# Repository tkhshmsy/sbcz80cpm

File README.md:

# sbcz80cpm
Single Board Computer with Z80 for CP/M

# Features
* Z80 cpu board for CP/M, without any ROM chips
  * supports 128KB to 512KB of SRAM, banked in 32KB
* ATMEGA4809 as I/O Engine sub system
  * Boot loader control
  * UART for console Input/Output
  * Floppy Disk Emulation with SD Card via SPI
  * RTC via I2C
  * other I2C devices

# PCB
## Schematics and Layout

## BOM
| Ref | Name | Qty | Description | Package | Link |
| --- | ---- | --- | ----------- | ------- | ---- |
| U1 | Z80 | 1 | Z80 CPU | DIP40 | Zilog Z84C00*, NEC uPD780C |
| U2 | 74HC32 | 1 | Quad OR | DIP14 | [akizuki](https://akizukidenshi.com/catalog/g/g112877/)|
| U3 | ATMEGA4809 | 1 | ATMEGA4809 | PDIP40 | [akizuki](https://akizukidenshi.com/catalog/g/g116144/)|
| U4 | AS6C4008 | 1 | SRAM | DIP32 | [mouser](https://www.mouser.jp/ProductDetail/Alliance-Memory/AS6C4008-55PCN?qs=E5c5%252Bmu3i3%252BMOyro1Tlhzg%3D%3D)|
| X1 | 1-10MHz | 1 | Crystal OSC | DIP8 | [akizuki 8MHz](https://akizukidenshi.com/catalog/g/g117022/), [akizuki 10MHz](https://akizukidenshi.com/catalog/g/g117023/)|
| C1, C2, C3, C4, C5, C6, C7, C8, C9 | 0.1uF | 9 | | ||
| C10  | 470uF    | 1 | | ||
| R1 | 1K-10K | 1 | for /WAIT control, 10K(-5MHz), 1K(8MHz-)| ||
| R2 | 10K | 1 | for pullup | ||
| R3, R4 | 10K | 2 | for I2C pullup | ||
| R5 | 1K | 1 | for LED | ||
| RN1 | 10Kx4 | 1 | for pullup | |[akizuki](https://akizukidenshi.com/catalog/g/g111909/)|
| RN2 | 10Kx4 | 1 | for IPL control | ||
| RN3 | 10Kx8 | 1 | for IPL control | |[akizuki](https://akizukidenshi.com/catalog/g/g111910/)|
| D1 | LED | 1 | 3mm | ||
| SW1 | Push Button | 1 | Reset SW| |[akizuki](https://akizukidenshi.com/catalog/g/g103647/)|
| J1, J2 | 1x6 Pin Socket | 2 | for SDCard, RTC | ||
| J3 | 1x4 Pin Socket | 1 | for I2C | pitch 2.54 ||
| J4 | 1x4 Pin Socket | 1 | for I2C | pitch 2.0 ||
| J5 | USB Type-C Power | 1 | for PowerSupply | |[akizuki](https://akizukidenshi.com/catalog/g/g116895/)|
| J6 | 1x3 Pin Socket | 1 | for UPDI | ||
| J7 | 1x6 Pin Header | 1 | for Serial comm | ||
| J8 | 2x13 Pin Header | 1 | for I/O Bus export | ||
| SDCard I/F | SD Card Module | 1 | | |[amazon.co.jp](https://www.amazon.co.jp/dp/B083DT3LQK)|
| RTC I/F | RTC Module | 1 | | |[amazon.co.jp](https://www.amazon.co.jp/dp/B081RJRB8N)|

## Memory Map

### System Memory
| Address | Size | Name | Note |
| ----- | ---- | ---- | ---- |
|0x0000 - 0x7FFF| 32KB | RAM | Banked memory selected with BANKSEL0-3 |
|0x8000 - 0xFFFF| 32KB | RAM | Fixed to "the tail of Banks" |

### SRAM Banks
* every 32KB, selected with BANKSEL0-3
  * Bank0 : 0x0000 - 0x7FFF
  * ...
* "the tail of Banks" which is mapped into 0x8000 - 0xFFFF on system
  * 128KB: 0x18000 - 0x1FFFF
  * 256KB: 0x28000 - 0x2FFFF
  * 512KB: 0x48000 - 0x4FFFF

# License
* MIT
  * contains follows
    * schematics and PCB
    * firmware `I/O Engine`
    * boot loaders and customized bios
  * the others are NOT included.

# Author
* [tkhshmsy@gmail.com](tkhshmsy@gmail.com)

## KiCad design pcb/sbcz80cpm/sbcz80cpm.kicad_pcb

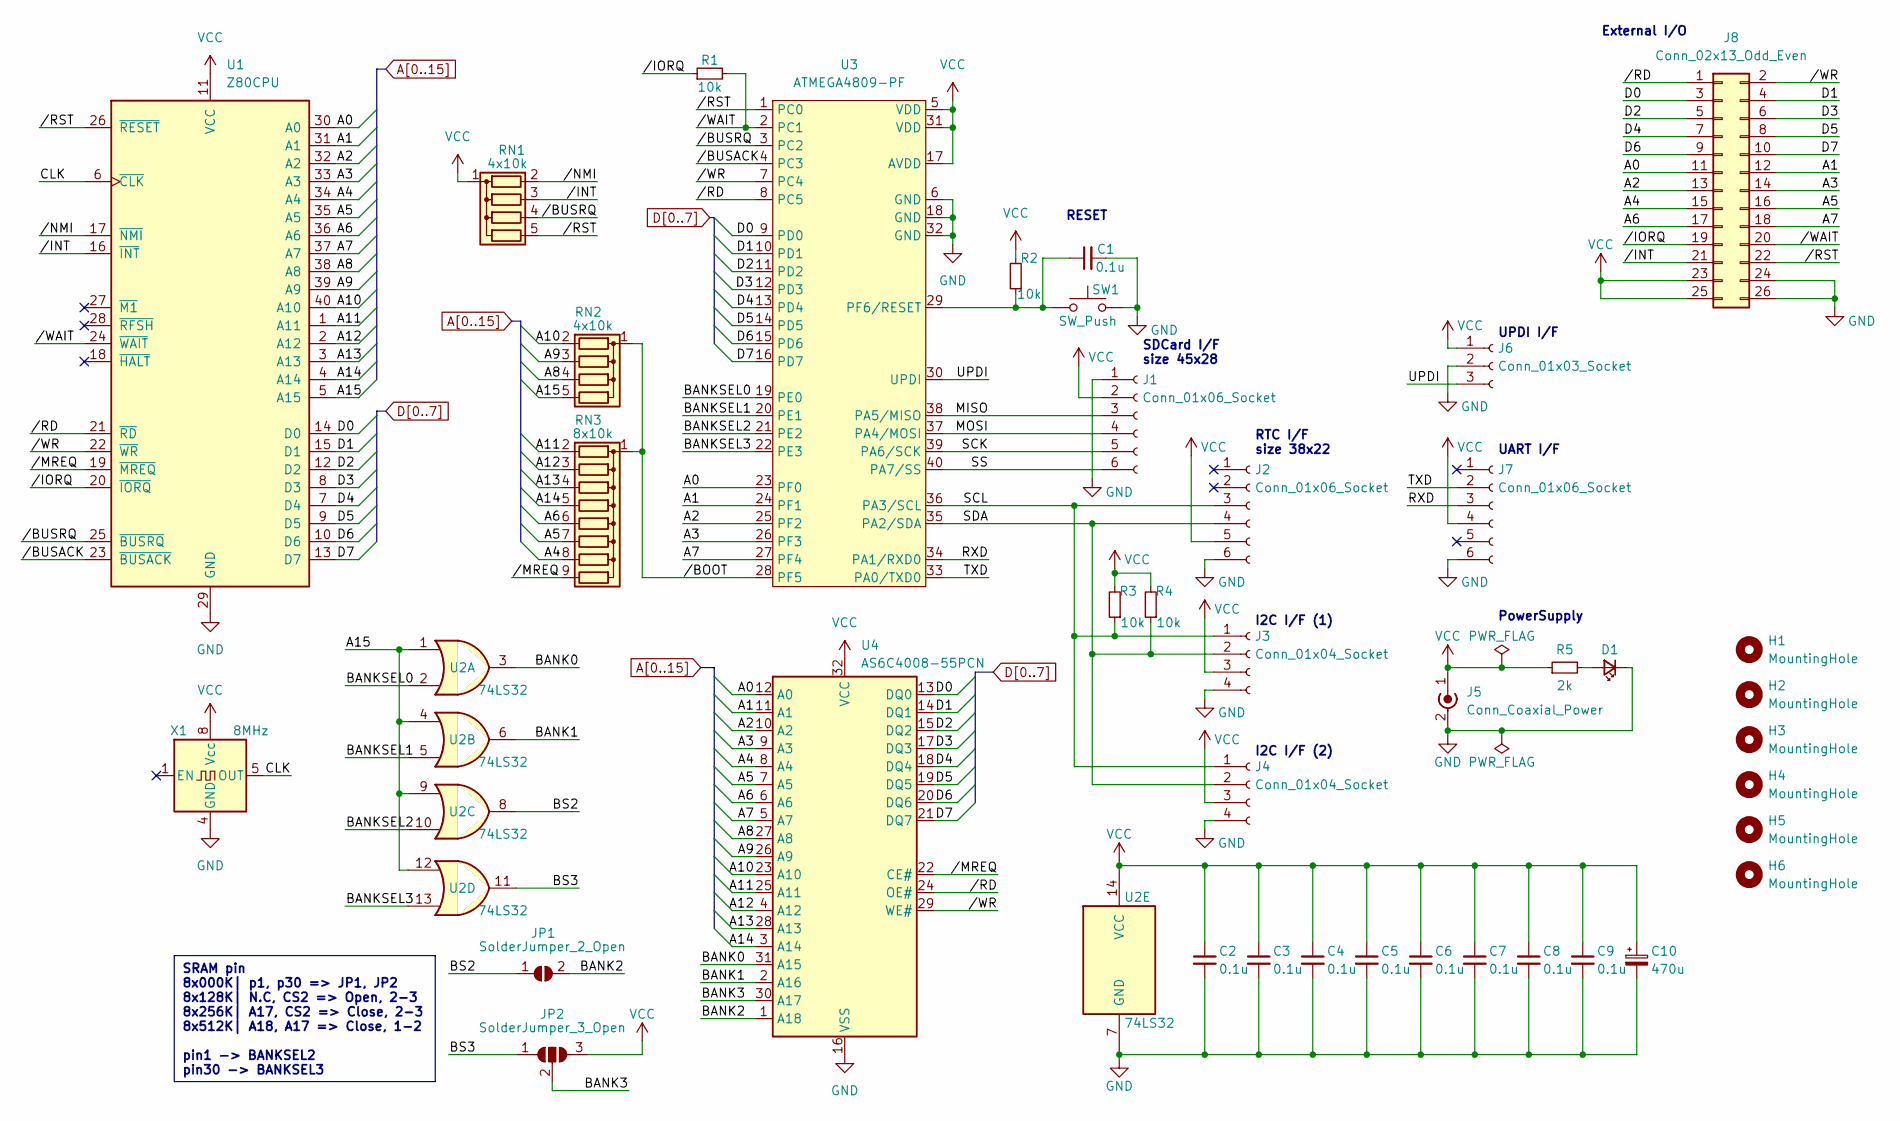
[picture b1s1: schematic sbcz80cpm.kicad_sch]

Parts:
C1, C2, C3, C4, C5, C6, C7, C8, C9: 0.1u; C_Disc_D4.3mm_W1.9mm_P5.00mm
C10: 470u; CP_Radial_D8.0mm_P5.00mm
D1: LED_Small; LED_D3.0mm
H1, H2, H3, H4, H5, H6: MountingHole; MountingHole_3.2mm_M3
J1, J2: Conn_01x06_Socket; PinSocket_1x06_P2.54mm_Vertical
J3: Conn_01x04_Socket; PinHeader_1x04_P2.54mm_Vertical
J4: Conn_01x04_Socket; PinHeader_1x04_P2.00mm_Vertical
J5: Conn_Coaxial_Power; A295-CTRPB-1
J6: Conn_01x03_Socket; UPDIconn
J7: Conn_01x06_Socket; PinHeader_1x06_P2.54mm_Vertical
J8: Conn_02x13_Odd_Even; PinHeader_2x13_P2.54mm_Vertical
JP1: SolderJumper_2_Open; SolderJumper-2_P1.3mm_Open_Pad1.0x1.5mm
JP2: SolderJumper_3_Open; SolderJumper-3_P1.3mm_Open_Pad1.0x1.5mm_NumberLabels
R1, R2, R3, R4: 10k; R_Axial_DIN0204_L3.6mm_D1.6mm_P7.62mm_Horizontal
R5: 2k; R_Axial_DIN0204_L3.6mm_D1.6mm_P7.62mm_Horizontal
RN1, RN2: 4x10k; R_Array_SIP5
RN3: 8x10k; R_Array_SIP9
SW1: SW_Push; SW_PUSH_6mm
U1: Z80CPU; DIP-40_W15.24mm_Socket
U2: 74LS32; DIP-14_W7.62mm_Socket
U3: ATMEGA4809-PF; DIP-40_W15.24mm_Socket
U4: AS6C4008-55PCN; DIP-32_W15.24mm_Socket
X1: 8MHz; Oscillator_DIP-8

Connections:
/BANK0: U2.3, U4.31 (A15)
/BANK1: U2.6, U4.2 (A16)
/BANK2: JP1.2 (B), U4.1 (A18)
/BANK3: JP2.2 (C), U4.30 (A17)
/BANKSEL0: U2.2, U3.19 (PE0)
/BANKSEL1: U2.5, U3.20 (PE1)
/BANKSEL2: U2.10, U3.21 (PE2)
/BANKSEL3: U2.13, U3.22 (PE3)
/BS2: JP1.1 (A), U2.8
/BS3: JP2.1 (A), U2.11
/CLK: U1.6 (~CLK), X1.5 (OUT)
/MISO: J1.3, U3.38 (PA5/MISO)
/MOSI: J1.4, U3.37 (PA4/MOSI)
/RXD: J7.3, U3.34 (PA1/RXD0)
/SCK: J1.5, U3.39 (PA6/SCK)
/SCL: J2.3, J3.1, J4.1, R3.1, U3.36 (PA3/SCL)
/SDA: J2.4, J3.2, J4.2, R4.1, U3.35 (PA2/SDA)
/SS: J1.6, U3.40 (PA7/SS)
/TXD: J7.2, U3.33 (PA0/TXD0)
/UPDI: J6.3, U3.30 (UPDI)
//BOOT: RN2.1 (common), RN3.1 (common), U3.28 (PF5)
//BUSACK: U1.23 (~BUSACK), U3.4 (PC3)
//BUSRQ: RN1.4 (R3), U1.25 (~BUSRQ), U3.3 (PC2)
//INT: J8.21, RN1.3 (R2), U1.16 (~INT)
//IORQ: J8.19, R1.1, U1.20 (~IORQ)
//MREQ: RN3.9 (R8), U1.19 (~MREQ), U4.22 (CE#)
//NMI: RN1.2 (R1), U1.17 (~NMI)
//RD: J8.1, U1.21 (~RD), U3.8 (PC5), U4.24 (OE#)
//RST: J8.22, RN1.5 (R4), U1.26 (~RESET), U3.1 (PC0)
//WAIT: J8.20, R1.2, U1.24 (~WAIT), U3.2 (PC1)
//WR: J8.2, U1.22 (~WR), U3.7 (PC4), U4.29 (WE#)
A0: J8.11, U1.30 (A0), U3.23 (PF0), U4.12 (A0)
A1: J8.12, U1.31 (A1), U3.24 (PF1), U4.11 (A1)
A2: J8.13, U1.32 (A2), U3.25 (PF2), U4.10 (A2)
A3: J8.14, U1.33 (A3), U3.26 (PF3), U4.9 (A3)
A4: J8.15, RN3.8 (R7), U1.34 (A4), U4.8 (A4)
A5: J8.16, RN3.7 (R6), U1.35 (A5), U4.7 (A5)
A6: J8.17, RN3.6 (R5), U1.36 (A6), U4.6 (A6)
A7: J8.18, U1.37 (A7), U3.27 (PF4), U4.5 (A7)
A8: RN2.4 (R3), U1.38 (A8), U4.27 (A8)
A9: RN2.3 (R2), U1.39 (A9), U4.26 (A9)
A10: RN2.2 (R1), U1.40 (A10), U4.23 (A10)
A11: RN3.2 (R1), U1.1 (A11), U4.25 (A11)
A12: RN3.3 (R2), U1.2 (A12), U4.4 (A12)
A13: RN3.4 (R3), U1.3 (A13), U4.28 (A13)
A14: RN3.5 (R4), U1.4 (A14), U4.3 (A14)
A15: RN2.5 (R4), U1.5 (A15), U2.1, U2.4, U2.9, U2.12
D0: J8.3, U1.14 (D0), U3.9 (PD0), U4.13 (DQ0)
D1: J8.4, U1.15 (D1), U3.10 (PD1), U4.14 (DQ1)
D2: J8.5, U1.12 (D2), U3.11 (PD2), U4.15 (DQ2)
D3: J8.6, U1.8 (D3), U3.12 (PD3), U4.17 (DQ3)
D4: J8.7, U1.7 (D4), U3.13 (PD4), U4.18 (DQ4)
D5: J8.8, U1.9 (D5), U3.14 (PD5), U4.19 (DQ5)
D6: J8.9, U1.10 (D6), U3.15 (PD6), U4.20 (DQ6)
D7: J8.10, U1.13 (D7), U3.16 (PD7), U4.21 (DQ7)
GND: C1.2, C2.2, C3.2, C4.2, C5.2, C6.2, C7.2, C8.2, C9.2, C10.2, D1.1 (K), J1.1, J2.6, J3.4, J4.4, J5.2 (Ext), J6.2, J7.6, J8.24, J8.26, SW1.2, U1.29 (GND), U2.7 (GND), U3.6 (GND), U3.18 (GND), U3.32 (GND), U4.16 (VSS), X1.4 (GND)
unnamed: D1.2 (A), R5.2
unnamed: C1.1, R2.1, SW1.1, U3.29 (PF6/RESET)
VCC: C2.1, C3.1, C4.1, C5.1, C6.1, C7.1, C8.1, C9.1, C10.1, J1.2, J2.5, J3.3, J4.3, J5.1 (In), J6.1, J7.4, J8.23, J8.25, JP2.3 (B), R2.2, R3.2, R4.2, R5.1, RN1.1 (common), U1.11 (VCC), U2.14 (VCC), U3.5 (VDD), U3.17 (AVDD), U3.31 (VDD), U4.32 (VCC), X1.8 (Vcc)

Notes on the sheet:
SRAM pin 8x000K| p1, p30 => JP1, JP2 8x128K| N.C, CS2 => Open, 2-3 8x256K| A17, CS2 => Close, 2-3 8x512K| A18, A17 => Close, 1-2 pin1 -> BANKSEL2 pin30 -> BANKSEL3
UART I/F
External I/O
PowerSupply
UPDI I/F
I2C I/F (1)
RESET
RTC I/F size 38x22
I2C I/F (2)
SDCard I/F size 45x28

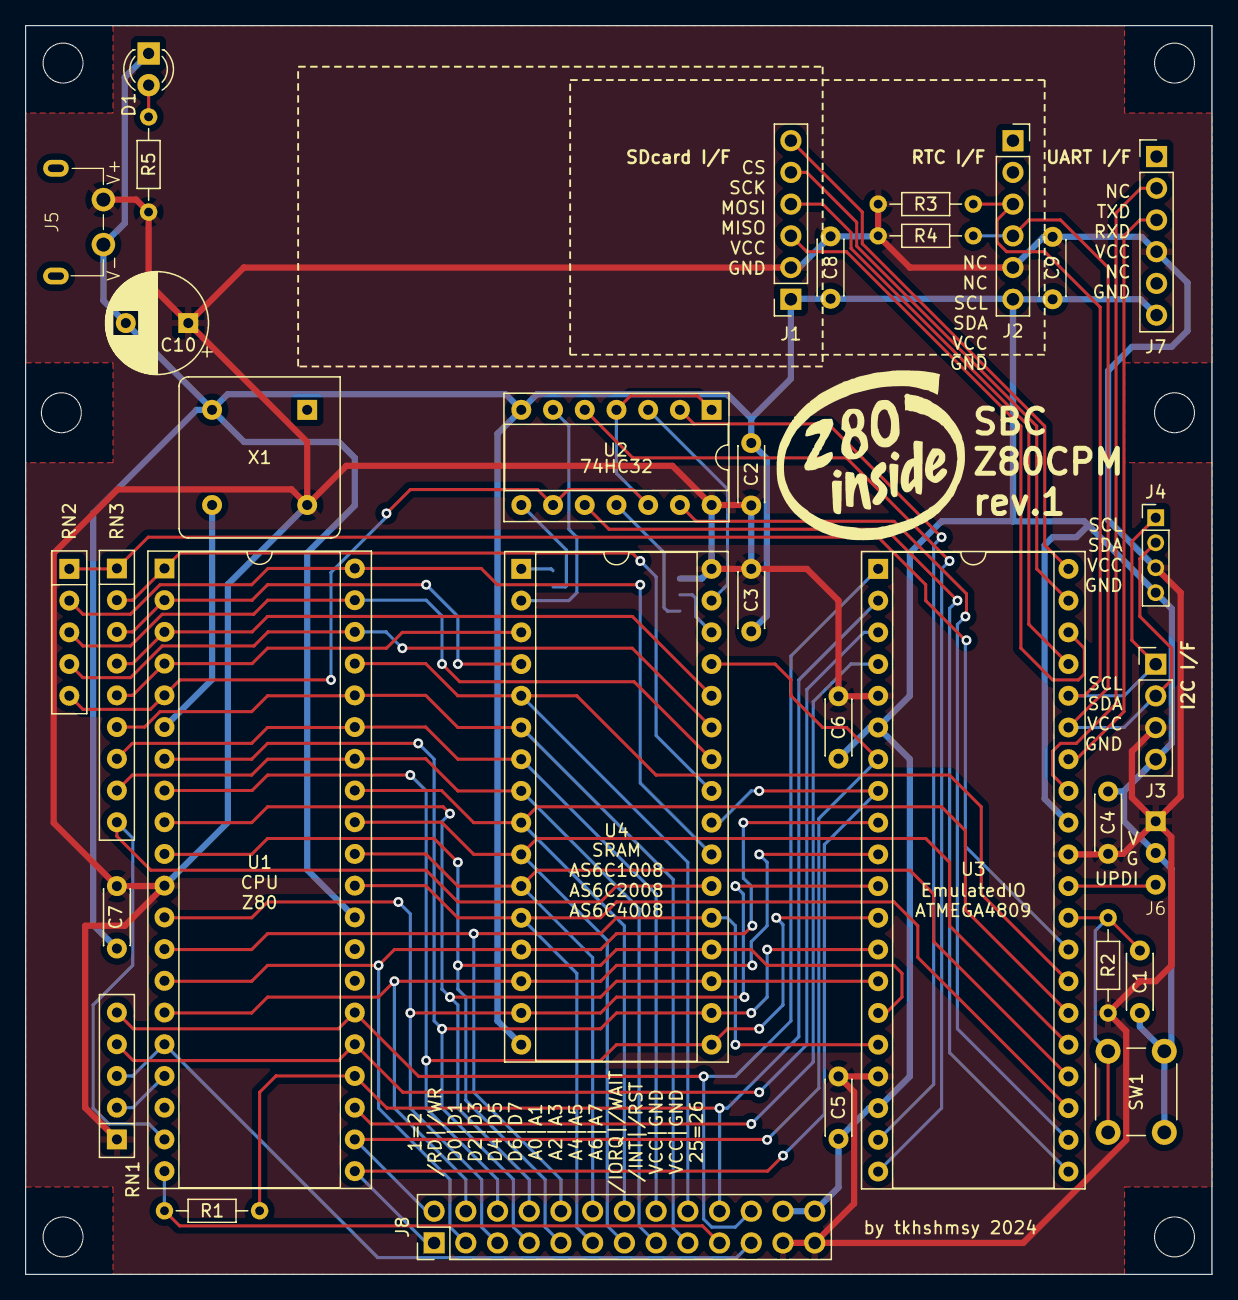
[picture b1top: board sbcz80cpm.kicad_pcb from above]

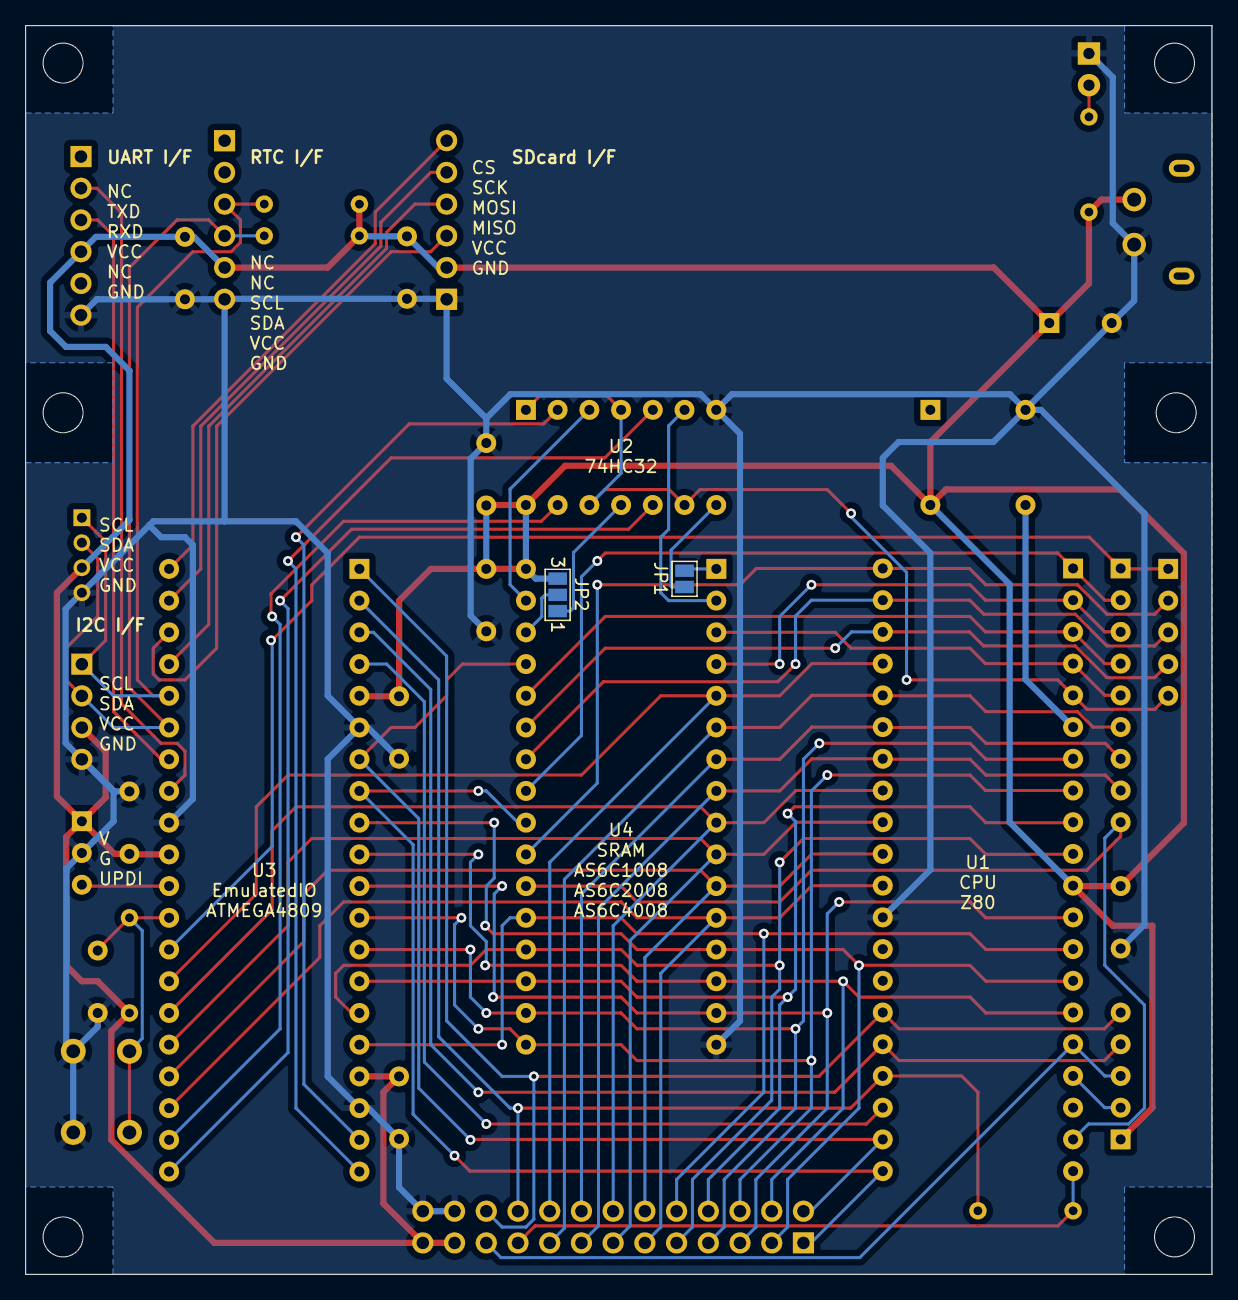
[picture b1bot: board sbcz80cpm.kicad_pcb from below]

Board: 2 copper layers, 95.0 x 100.0 mm, 41 parts (2 on the bottom side), 59 nets.

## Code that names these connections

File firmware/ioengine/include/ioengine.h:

#ifndef __EMULATED_IO_H__
#define __EMULATED_IO_H__

#include <avr/io.h>

#define EIO_VERSION "0.1.0"

#define Z80_RST PIN_PC0
#define Z80_WAIT PIN_PC1
#define Z80_BUSREQ PIN_PC2
#define Z80_BUSACK PIN_PC3
#define Z80_WR PIN_PC4
#define Z80_RD PIN_PC5

// PD0-7 = Z80D0-7
#define Z80_DATA PORTD
// PE0-3 = BANKSEL0-3
#define BANKSEL PORTE
// PF0-3 = Z80A0-3
#define Z80_ADDRESS PORTF
// PF4   = Z80A7
#define Z80_A7 PIN_PF4
#define BOOT_SEL PIN_PF5

#define UART_TX0 PIN_PA0
#define UART_RX0 PIN_PA1
#define I2C_SDA PIN_PA2
#define I2C_SCL PIN_PA3
#define SPI_MOSI PIN_PA4
#define SPI_MISO PIN_PA5
#define SPI_SCK PIN_PA6
#define SPI_SS PIN_PA7

#endif // __EMULATED_IO_H__

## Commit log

2024-09-12 Add PCB rev.1
2024-09-13 Fix README for rev.1
2024-11-05 Add firmware
    - ioengine v0.1.0
    - boot loaders
2024-11-05 Add basic
    - init code for NASCOM BASIC 4.7b
2024-11-05 Fix typo
2024-11-06 Add cpm22
    - BIOS for 62K CP/M ver 2.2
    - supports ibm-3740 formatted disk image
    - supports 4 disks
    - boot loader for BIOS
2024-11-06 Fix basic README
2024-11-06 Fix ioengine README
2024-11-07 Add examples/sdcard
2024-11-07 Fix ioengine README
    - Requirements
    - Build
2024-11-11 Fix README and others
2024-11-11 Add photo
